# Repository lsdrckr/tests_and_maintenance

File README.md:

# Tests réalisés sur la carte

## Tests éléctronique
Nous avons testé au multimètre si les différents ground et 3,3V étaient reliés entre eux. Nous avons réalisés le même tests sur les différents pins du circuit.
Pour vérifier la qualité de notre soudure, nous avons vérifié qu'il n'y ai aucun court circuit et les valeurs des différents composants (résistances et capacités).
En regardant au microscope et en testant, on a remarqué quelques courts-circuits que nous avons immédiatement resoudé.

Nous avons cependant fait un grave erreur dès le schematic de notre carte : nous avons connecté les ports SWCLK et SWDIO sur les mauvais ports, ce qui empêchait le bon fonctionnement de la carte... Nous avons dû improvisé en créant des pistes volantes pour bien les connecter.

La photo ci-dessous montre le routage de SWCLK et SWDIO sur les pins 19 et 20 du stm32f030f4. Ils ne sont là que pour garder en tête les correction à faire dans le cas d'un second prototypage.

## Tests informatiques

A l'aide de la documentation fournis sur le site : https://linuxembedded.fr/2021/02/bare-metal-from-zero-to-blink, nous avons réaliser un Startup file nommé stm32_startup.c permettant de bien définir l'environnement pour le code main().
Il permet entre autre de gérer les handler du stm32f030f4 et d'attribuer les bonnes fonctions aux handler.

Nous avons ensuite créer le Linker cript nommé stm32_ls.ld qui permet de déterminer les adresses absolues des différentes sections en faisant référence aux informations mentionnées dans le Linker script.

Nous avons ensuite effectuer les modification necessaire pour permettre l'utilisation d'OpenOCD avec la carte : https://www.radioshuttle.de/en/turtle-en/nucleo-st-link-interface-en/

## Résultats et axes d'améliorations

Photos de la cartes finale soudées.

Photos de l'écran lors du lancement de la commande make load.

On observe bien la bonne détection de la carte.

Vidéo de la carte lors du test avec OpenOCD.

Nous avons trouver ce projet fort enrichissant mais il manque à notre sens, cruellement de temps pour pouvoir effectuer le code et tous les tests unitaires nécessaire au test complet de la carte. Cependant le projet fût très enrichissant et à permis de mettre en pratique les connaissances vues en cours de TMS.

Le pipeline du Gitlab-CI se résume à un cpp-check suivi d'une étape de build et d'une étape de lint.

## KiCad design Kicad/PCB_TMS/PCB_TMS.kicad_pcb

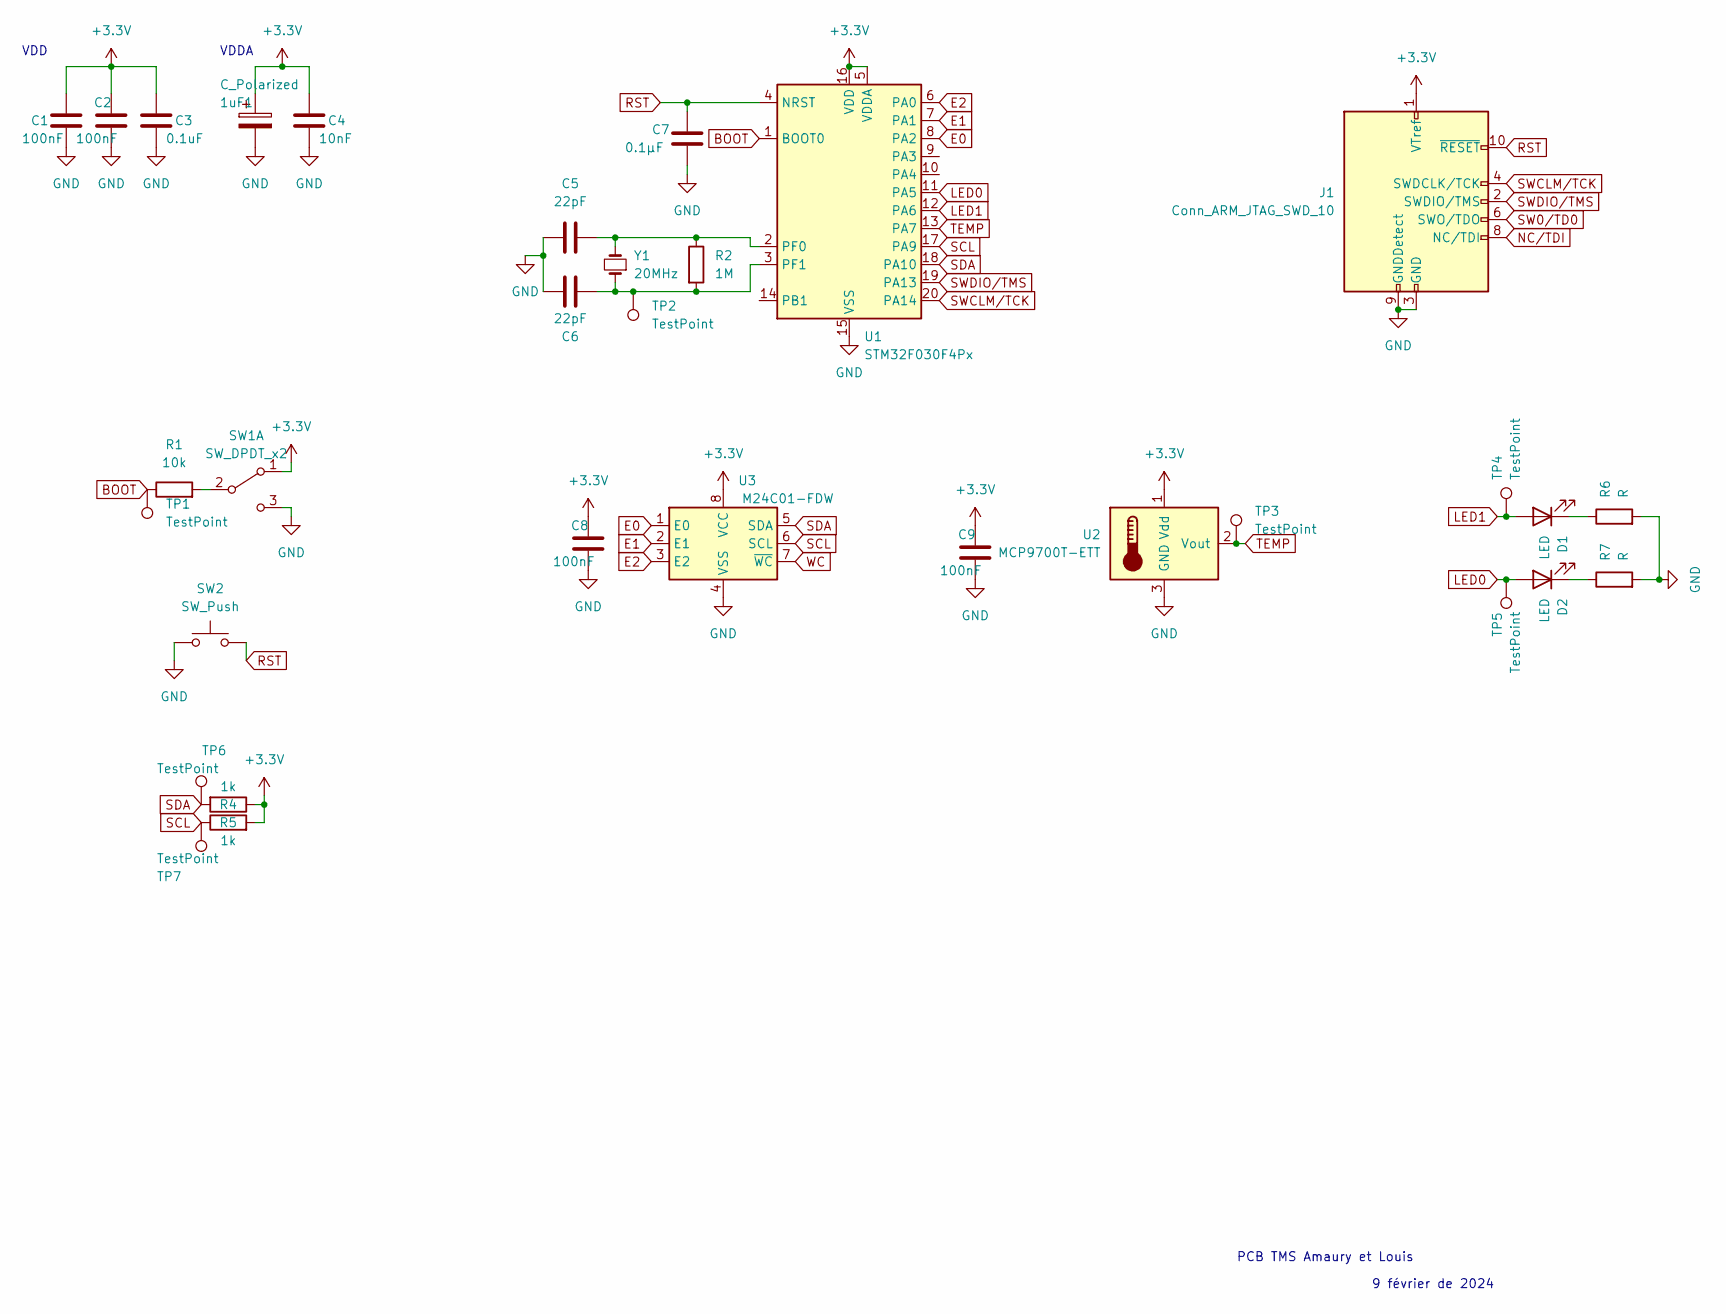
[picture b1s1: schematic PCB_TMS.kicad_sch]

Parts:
1uF1: C_Polarized; C_0603_1608Metric_Pad1.08x0.95mm_HandSolder
C1, C2, C8, C9: 100nF; C_0603_1608Metric_Pad1.08x0.95mm_HandSolder
C3: 0.1uF; C_0603_1608Metric_Pad1.08x0.95mm_HandSolder
C4: 10nF; C_0603_1608Metric_Pad1.08x0.95mm_HandSolder
C5, C6: 22pF; C_0603_1608Metric_Pad1.08x0.95mm_HandSolder
C7: 0.1µF; C_0603_1608Metric_Pad1.08x0.95mm_HandSolder
D1, D2: LED; D_0603_1608Metric_Pad1.05x0.95mm_HandSolder
J1: Conn_ARM_JTAG_SWD_10; PinHeader_2x05_P2.54mm_Vertical
R1: 10k; R_0603_1608Metric_Pad0.98x0.95mm_HandSolder
R2: 1M; R_0603_1608Metric_Pad0.98x0.95mm_HandSolder
R4, R5: 1k; R_0603_1608Metric_Pad0.98x0.95mm_HandSolder
R6, R7: R; R_0603_1608Metric_Pad0.98x0.95mm_HandSolder
SW1: SW_DPDT_x2; PinHeader_1x03_P2.54mm_Vertical
SW2: SW_Push; SW_SPST_SKQG_WithStem
TP1, TP2, TP3, TP4, TP5, TP6, TP7: TestPoint; TestPoint_Pad_D1.0mm
U1: STM32F030F4Px; TSSOP-20_4.4x6.5mm_P0.65mm
U2: MCP9700T-ETT; SOT-23
U3: M24C01-FDW; TSSOP-8_4.4x3mm_P0.65mm
Y1: 20MHz; Crystal_SMD_HC49-SD_HandSoldering

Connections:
+3.3V: 1uF1.1, C1.2, C2.2, C3.2, C4.2, C8.2, C9.2, J1.1 (VTref), R4.1, R5.2, SW1.1 (A), U1.5 (VDDA), U1.16 (VDD), U2.1 (Vdd), U3.8 (VCC)
BOOT: R1.1, TP1.1, U1.1 (BOOT0)
E0: U1.8 (PA2), U3.1 (E0)
E1: U1.7 (PA1), U3.2 (E1)
E2: U1.6 (PA0), U3.3 (E2)
GND: 1uF1.2, C1.1, C2.1, C3.1, C4.1, C5.1, C6.1, C7.1, C8.1, C9.1, J1.3 (GND), J1.5 (GND), J1.9 (GNDDetect), R6.2, R7.2, SW1.3 (C), SW2.1, U1.15 (VSS), U2.3 (GND), U3.4 (VSS)
LED0: D2.2 (A), TP5.1, U1.11 (PA5)
LED1: D1.2 (A), TP4.1, U1.12 (PA6)
NC/TDI: J1.8 (NC/TDI)
unnamed: C5.2, R2.1, U1.2 (PF0), Y1.2
unnamed: C6.2, R2.2, TP2.1, U1.3 (PF1), Y1.1
unnamed: D1.1 (K), R6.1
unnamed: D2.1 (K), R7.1
unnamed: R1.2, SW1.2 (B)
RST: C7.2, J1.10 (~RESET), SW2.2, U1.4 (NRST)
SCL: R5.1, TP7.1, U1.17 (PA9), U3.6 (SCL)
SDA: R4.2, TP6.1, U1.18 (PA10), U3.5 (SDA)
SW0/TD0: J1.6 (SWO/TDO)
SWCLM/TCK: J1.4 (SWDCLK/TCK), U1.20 (PA14)
SWDIO/TMS: J1.2 (SWDIO/TMS), U1.19 (PA13)
TEMP: TP3.1, U1.13 (PA7), U2.2 (Vout)
WC: U3.7 (~WC)

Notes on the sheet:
VDDA
9 février de 2024
VDD
PCB TMS Amaury et Louis

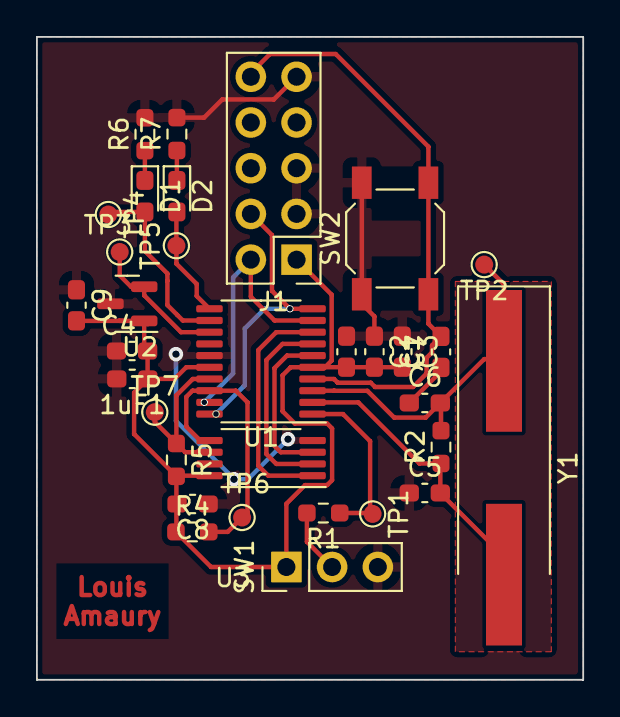
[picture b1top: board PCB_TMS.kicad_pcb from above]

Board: 2 copper layers, 30.3 x 35.7 mm, 32 parts (0 on the bottom side), 19 nets.

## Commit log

2024-02-09 Création du projet kicad
2024-02-09 Datasheet
2024-02-09 readme1
2024-02-09 Fin schematic
2024-02-09 Début routage
2024-02-17 Routage v1
2024-02-19 Changement d'empreintes
2024-02-20 PCB Routage fini
2024-02-21 Génération gerber
2024-02-21 Génération gerber (bonne)
2024-02-22 Linker
2024-02-23 Fichier yml
2024-02-23 correction
2024-02-23 correction CI
2024-02-23 yml v3
2024-02-23 Pipelines V4
2024-02-23 Ajout README.md
2024-02-23 Modif README.md
2024-03-04 correction PCB
2024-03-04 correction README
2024-03-04 correction README V2
2024-03-04 correction README V3
2024-03-05 yml fonctionnel V1
